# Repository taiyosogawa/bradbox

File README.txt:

==========
= README =
==========
Author: Taiyo Sogawa
Last Revised: 3/17/2013

=======================
= System Requirements =
=======================
Device: Windows XP 32-bit Operating System

1) Install Java SE 7 JRE
	See:	<http://www.oracle.com/technetwork/java/javase/downloads/index.html>

============================
= Application Installation =
============================

1) Double click on Install_Brad_Box.exe
	This should automatically:
		Put the platform-tools directory in the root directory (Do not delete C:\platform-tools after installation!)
		Put rxtxSerial.dll, sqlite3.def, sqlite3.dll, and sqlite3.exe in C:\WINDOWS\System32
		Put an "Brad Box.exe" on the desktop
	If anything fails, make sure these files are located in the appropriate directories. Manually copying the files might be necessary.

========================
= Arduino Installation =
========================
Device: Arduino Micro

1) Install Driver for Arduino Micro 
	Drivers are located in the setup/arduino-drivers directory 
2) Change device port to COM34
	Control Panel > System Properties > Device Manager
	Find Arduino Micro under Ports
	Right Click > Properties > Port Settings > Advanced
	Change port number to COM34

========================
= Android Installation =
========================
Device: Unlocked Samsung Galaxy Pocket S5300

1) Install phone drivers on computer (Directions vary by device.)
	Drivers for Galaxy Pocket are in the setup/android-drivers directory
2) Factory reset the phone if desired (Directions vary by device.)
	On the Galaxy Pocket, Dial *2767*3855#
3) Root the android phone (Directions vary by device.)
4) Enable USB Debug Mode (Directions vary by device.)
	On the Galaxy Pocket, Settings > Applications > Development > USB debugging 
5) Install Android application
	Connect phone to computer by USB
	You can check the connection by opening CMD, navigating to C:\platform-tools and typing command "adb devices"
	Double click install_new_android_application.exe in C:\platform-tools when phone connected
	You will see the Brad Box logo on the phone screen on a successful install

============================
= Additional Documentation =
============================

https://code.google.com/p/aster/source/browse/src/com/android/chimpchat/core/IChimpDevice.java?r=967f7f8cd6249c69e00c6de7ff1b55bd0f51d311

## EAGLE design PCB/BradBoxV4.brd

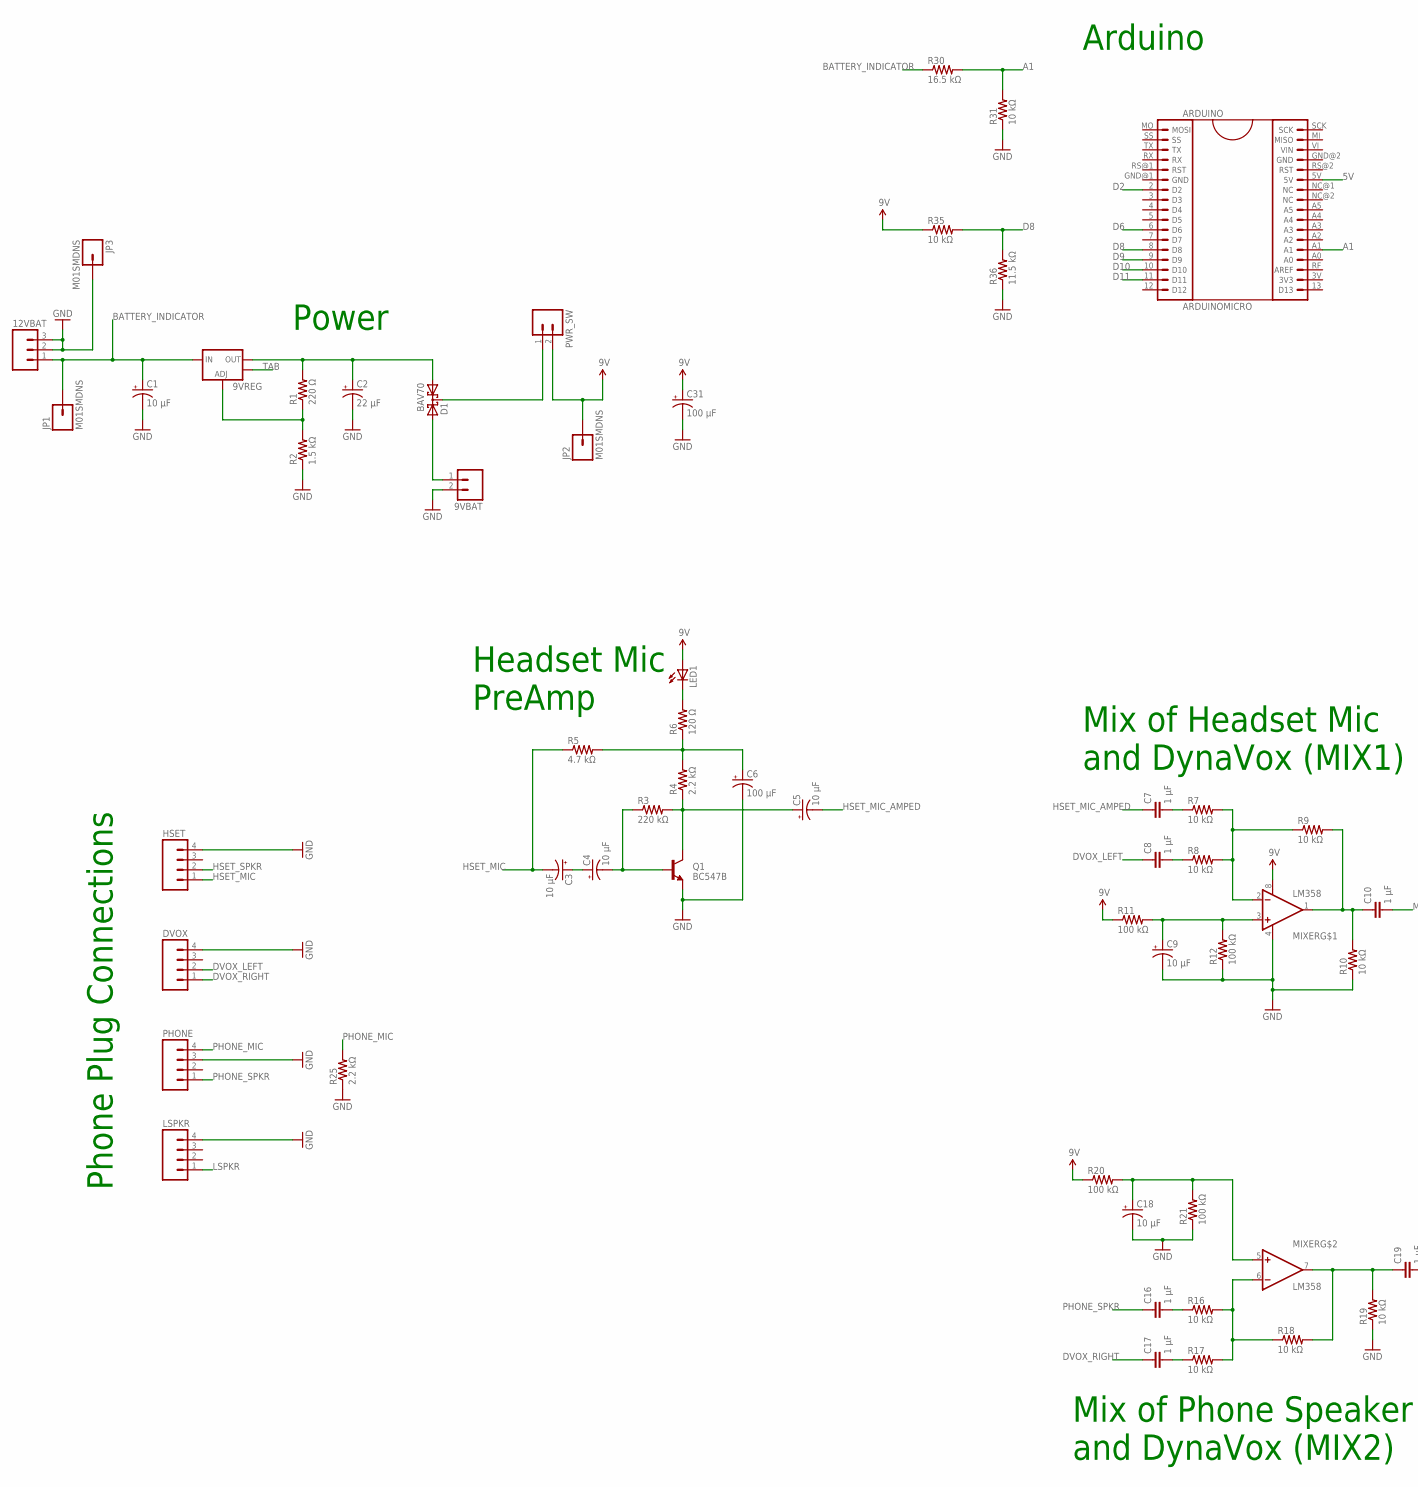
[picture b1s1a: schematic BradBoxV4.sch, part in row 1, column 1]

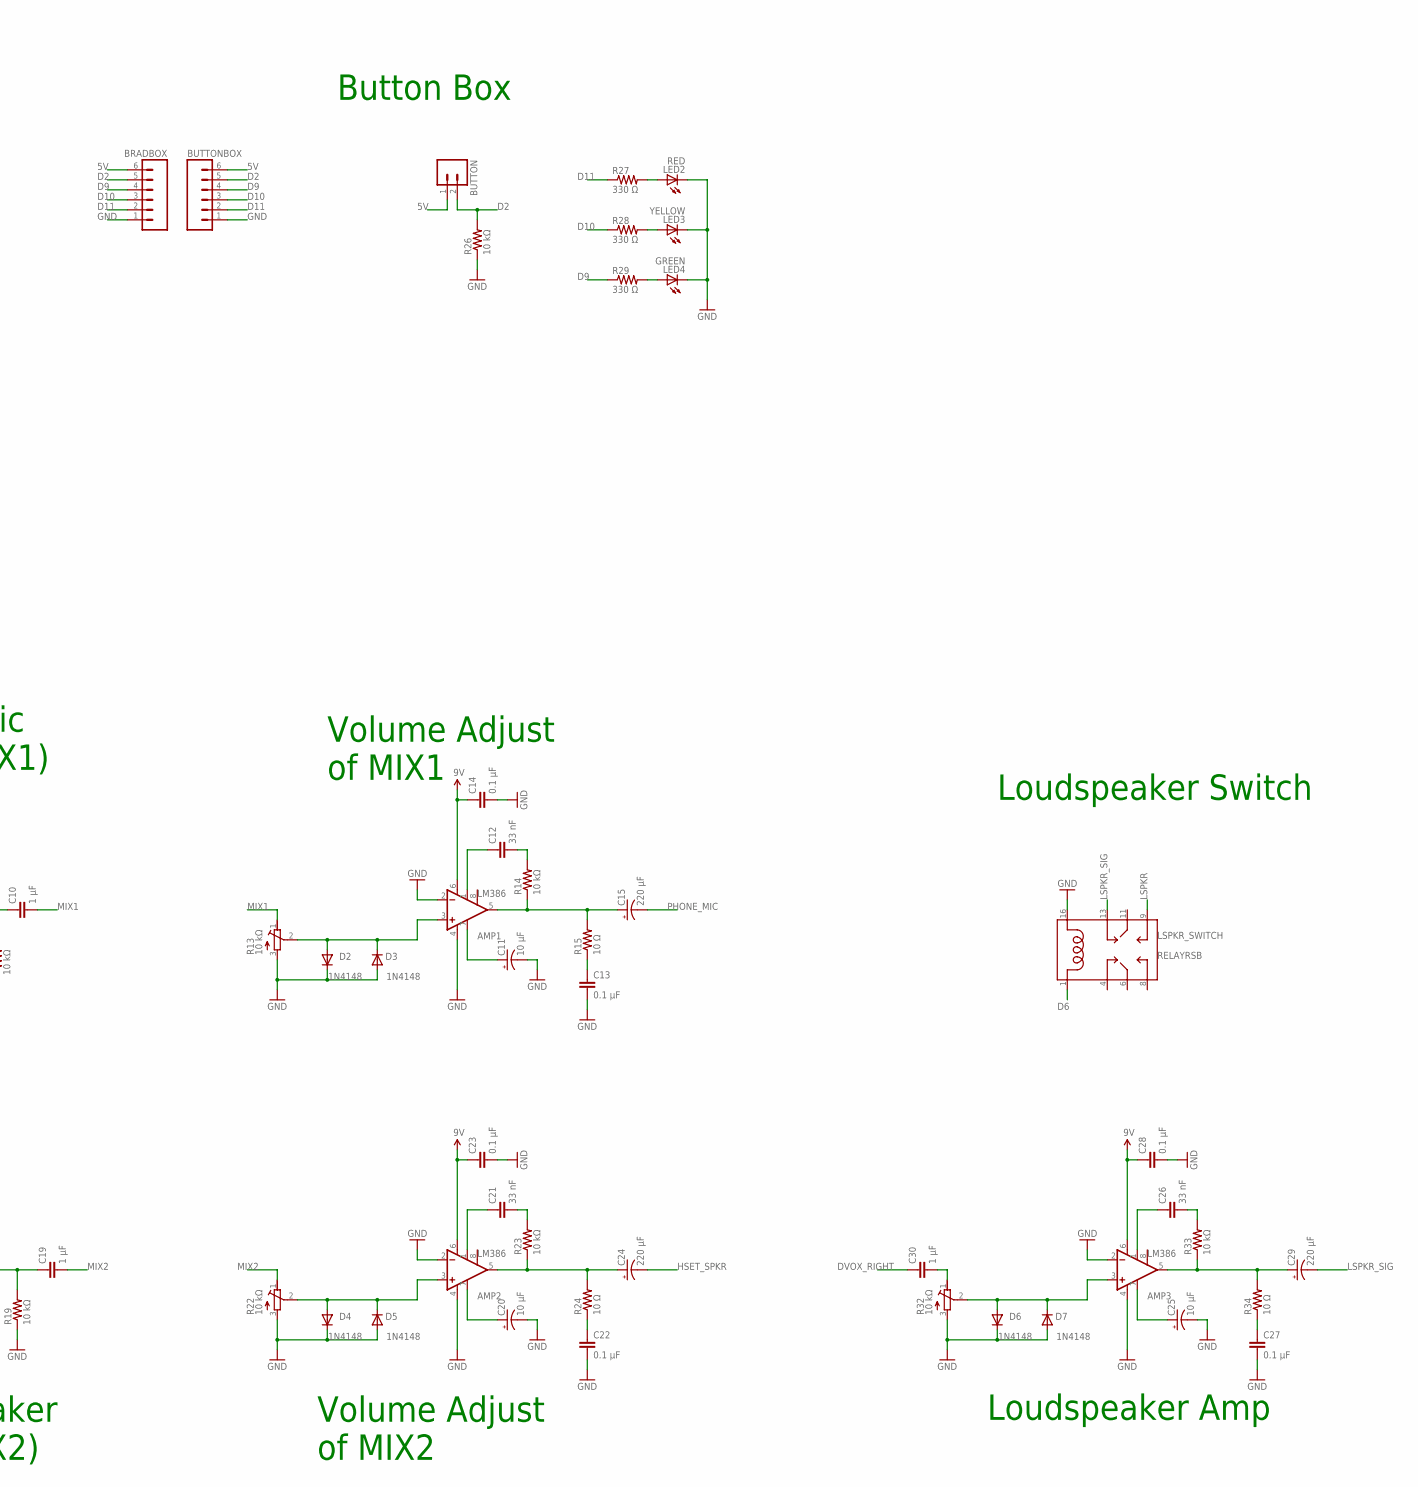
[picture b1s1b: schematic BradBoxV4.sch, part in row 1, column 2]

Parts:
9VBAT: M02POLAR; MOLEX-1X2
9VREG: V_REG_LM1117SOT223; SOT223
12VBAT: M03POLAR; MOLEX-1X3
AMP1, AMP2, AMP3: LM386; DIP08
ARDUINO: ARDUINOMICRO; ARDUINO_MICRO
BRADBOX: M06POLAR; MOLEX-1X6
BUTTON: M02POLAR; MOLEX-1X2
BUTTONBOX: M06POLAR; MOLEX-1X6
C1, C3, C4, C5, C9, C11, C18, C20, C25: 10 µF; 0603-CAP-POL
C2: 22 µF; 0603-CAP-POL
C6, C31: 100 µF; CPOL-RADIAL-100UF-100V
C7, C8, C10, C16, C17, C19, C30: 1 µF; 0603-CAP
C12, C21, C26: 33 nF; 0603-CAP
C13, C14, C22, C23, C27, C28: 0.1 µF; 0603-CAP
C15, C24, C29: 220 µF; CPOL-RADIAL-220UF-100V
D1: BAV70; SOT23
D2, D3, D4, D5, D6, D7: 1N4148; SOD523F
DVOX: M04POLAR; MOLEX-1X4
HSET: M04POLAR; MOLEX-1X4
JP1, JP2, JP3: M01SMDNS; 1X01NS
LED1: LED0603; LED-0603
LED2: RED; LED5MM
LED3: YELLOW; LED5MM
LED4: GREEN; LED5MM
LSPKR: M04POLAR; MOLEX-1X4
LSPKR_SWITCH: RELAYRSB; RELAY-RSB
MIXER: LM358; DIP08
PHONE: M04POLAR; MOLEX-1X4
PWR_SW: M02POLAR; MOLEX-1X2
Q1: BC547B; TO-92-AMMO
R1: 220 Ω; R0603
R2: 1.5 kΩ; R0603
R3: 220 kΩ; R0603
R4, R25: 2.2 kΩ; R0603
R5: 4.7 kΩ; R0603
R6: 120 Ω; R0603
R7, R8, R9, R10, R14, R16, R17, R18, R19, R23, R26, R31, R33, R35: 10 kΩ; R0603
R11, R12, R20, R21: 100 kΩ; R0603
R13, R22, R32: 10 kΩ; RTRIMT93YA
R15, R24, R34: 10 Ω; R0603
R27, R28, R29: 330 Ω; R0603
R30: 16.5 kΩ; R0603
R36: 11.5 kΩ; R0603

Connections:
5V: ARDUINO.5V, BRADBOX.6, BUTTON.1, BUTTONBOX.6
9V: AMP1.6 (V+), AMP2.6 (V+), AMP3.6 (V+), C14.1, C23.1, C28.1, C31.1 (+), JP2.1, LED1.A, MIXER.8 (V+), PWR_SW.2, R11.1, R20.1, R35.1
A1: ARDUINO.A1, R30.2, R31.2
BATTERY_INDICATOR: 9VREG.3 (IN), 12VBAT.1, C1.1 (+), JP1.1, R30.1
D2: ARDUINO.2 (D2), BRADBOX.5, BUTTON.2, BUTTONBOX.5, R26.2
D6: ARDUINO.6 (D6), LSPKR_SWITCH.1
D8: ARDUINO.8 (D8), R35.2, R36.2
D9: ARDUINO.9 (D9), BRADBOX.4, BUTTONBOX.4, R29.1
D10: ARDUINO.10 (D10), BRADBOX.3, BUTTONBOX.3, R28.1
D11: ARDUINO.11 (D11), BRADBOX.2, BUTTONBOX.2, R27.1
DVOX_LEFT: C8.1, DVOX.2
DVOX_RIGHT: C17.1, C30.1, DVOX.1
GND: 9VBAT.2, 12VBAT.2, 12VBAT.3, AMP1.2 (-IN), AMP1.4 (V-), AMP2.2 (-IN), AMP2.4 (V-), AMP3.2 (-IN), AMP3.4 (V-), BRADBOX.1, BUTTONBOX.1, C1.2 (-), C2.2 (-), C6.2 (-), C9.2 (-), C11.2 (-), C13.2, C14.2, C18.2 (-), C20.2 (-), C22.2, C23.2, C25.2 (-), C27.2, C28.2, C31.2 (-), D2.C, D3.A, D4.C, D5.A, D6.C, D7.A, DVOX.4, HSET.4, JP3.1, LED2.K (C), LED3.K (C), LED4.K (C), LSPKR.4, LSPKR_SWITCH.16, MIXER.4 (V-), PHONE.3, Q1.1 (E), R2.1, R10.1, R12.1, R13.3 (E), R19.1, R21.1, R22.3 (E), R25.1, R26.1, R31.1, R32.3 (E), R36.1
HSET_MIC: C3.2 (-), HSET.1, R5.1
HSET_MIC_AMPED: C5.2 (-), C7.1
HSET_SPKR: C24.2 (-), HSET.2
LSPKR: LSPKR.1, LSPKR_SWITCH.9
LSPKR_SIG: C29.2 (-), LSPKR_SWITCH.13
MIX1: C10.2, R13.1 (A)
MIX2: C19.2, R22.1 (A)
unnamed: 9VREG.2 (OUT), C2.1 (+), D1.1 (A1), R1.2
unnamed: 9VREG.1 (ADJ), R1.1, R2.2
unnamed: AMP3.3 (+IN), D6.A, D7.C, R32.2 (S)
unnamed: D1.3 (C), PWR_SW.1
unnamed: 9VBAT.1, D1.2 (A2)
unnamed: C3.1 (+), C4.1 (+)
unnamed: C4.2 (-), Q1.2 (B), R3.1
unnamed: C5.1 (+), Q1.3 (C), R3.2, R4.1
unnamed: LED1.C, R6.2
unnamed: C6.1 (+), R4.2, R5.2, R6.1
unnamed: C8.2, R8.1
unnamed: C7.2, R7.1
unnamed: MIXER.2 (-IN), R7.2, R8.2, R9.1
unnamed: C10.1, MIXER.1 (OUT), R9.2, R10.2
unnamed: C9.1 (+), MIXER.3 (+IN), R11.2, R12.2
unnamed: AMP1.1 (GAIN), C12.1
unnamed: C12.2, R14.2
unnamed: AMP1.3 (+IN), D2.A, D3.C, R13.2 (S)
unnamed: AMP1.5 (OUT), C15.1 (+), R14.1, R15.2
unnamed: AMP1.7 (BP), C11.1 (+)
unnamed: C13.1, R15.1
unnamed: C17.2, R17.1
unnamed: C16.2, R16.1
unnamed: C18.1 (+), MIXER.5 (+IN), R20.2, R21.2
unnamed: MIXER.6 (-IN), R16.2, R17.2, R18.1
unnamed: C19.1, MIXER.7 (OUT), R18.2, R19.2
unnamed: AMP2.3 (+IN), D4.A, D5.C, R22.2 (S)
unnamed: AMP2.7 (BP), C20.1 (+)
unnamed: AMP2.1 (GAIN), C21.1
unnamed: C21.2, R23.2
unnamed: AMP2.5 (OUT), C24.1 (+), R23.1, R24.2
unnamed: C22.1, R24.1
unnamed: LED2.A, R27.2
unnamed: LED3.A, R28.2
unnamed: LED4.A, R29.2
unnamed: AMP3.7 (BP), C25.1 (+)
unnamed: AMP3.1 (GAIN), C26.1
unnamed: C26.2, R33.2
unnamed: AMP3.5 (OUT), C29.1 (+), R33.1, R34.2
unnamed: C27.1, R34.1
unnamed: C30.2, R32.1 (A)
PHONE_MIC: C15.2 (-), PHONE.4, R25.2
PHONE_SPKR: C16.1, PHONE.1
TAB: 9VREG.4 (OUT)

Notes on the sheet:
Phone Plug Connections
Power
Headset Mic PreAmp
Mix of Headset Mic and DynaVox (MIX1)
Volume Adjust of MIX1
Mix of Phone Speaker and DynaVox (MIX2)
Volume Adjust of MIX2
Arduino
Button Box
Loudspeaker Amp
Loudspeaker Switch

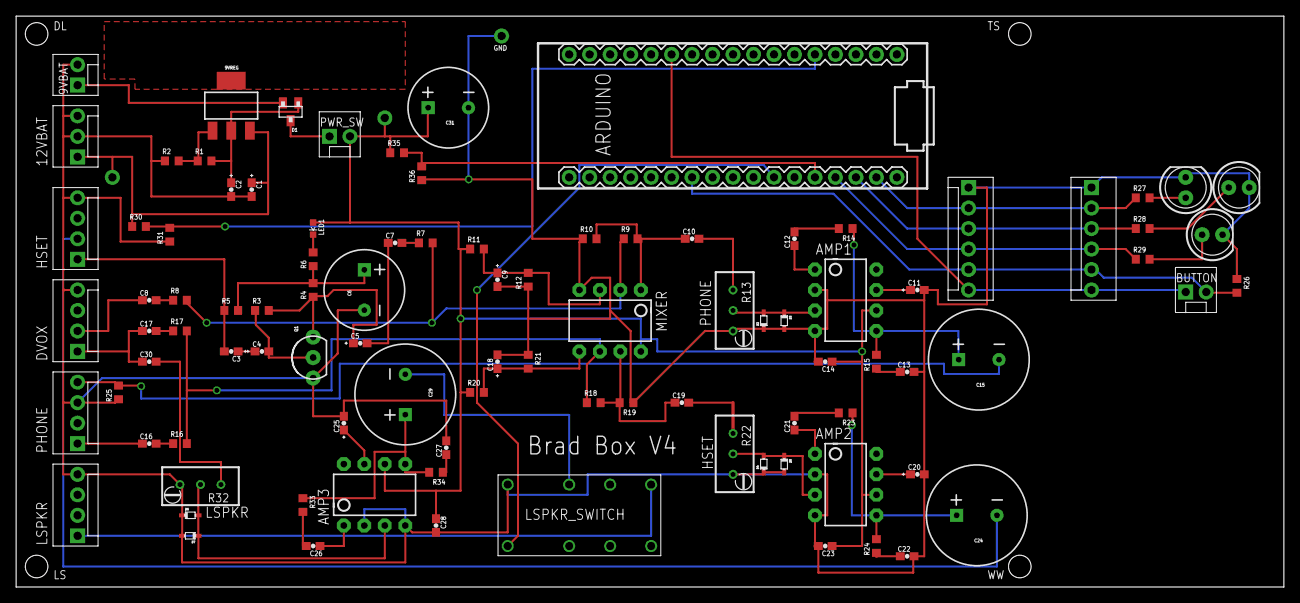
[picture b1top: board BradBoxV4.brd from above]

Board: 2 copper layers, 157.2 x 70.8 mm, 99 parts (0 on the bottom side), 63 nets.

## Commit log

2013-01-28 First commit with Java
2013-01-28 Calls can now be initiated and ended correctly
2013-01-28 Button push from Arduino will push the call button on the phone
2013-01-30 created separate classes for SuperFrame and KeypadPanel
2013-01-30 call, end call are public functions, Interface Constants defined
2013-02-04 Long button presses will restart the phone.
2013-02-04 can send hardcoded sms
2013-02-04 can send dynamic sms to phone numbers
2013-02-04 Changed navigation button icons
2013-02-04 Added all images for navigation buttons
2013-02-06 Grouped JToggleButtons
2013-02-06 Changed Look and Feel
2013-02-06 Added texting button
2013-02-06 added texting images
2013-02-18 removed platform-tools from project
2013-02-18 texting panel.
2013-02-21 Changed Keypad Button Sizes
2013-02-23 keypad shows up on phone when switching to keypad panel
2013-02-23 added images
2013-02-24 Device restarts with long button press
2013-02-24 contacts database automatically copies when a contact is added
2013-02-25 can search for contacts when pushing search button
2013-02-25 Added readme
2013-03-03 Loudspeaker controlled from options menu (pin 3 high = loudspeaker on)
2013-03-03 keys perform search query by name or number
2013-03-04 favorites or top 3 search results displayed on keypadPanel
2013-03-04 call button on ContactModule will dial and call correct number
2013-03-04 will delete up to 10 extra digits on phone before dialing
2013-03-04 Contacts can be deleted through editContactPanel
2013-03-04 Contacts edited by deleting old contact then creating new contact with new information.
2013-03-10 interface layout updated
2013-03-11 phone wakes up and unlocks when dialing.
2013-03-11 contacts can be saved as favorites
2013-03-11 Favorites added, edited, and deleted properly.
2013-03-15 Panels use consistent navigation
2013-03-15 fixed adding new contact as favorite
2013-03-15 Volume Panel works
2013-03-16 numbers prettified
2013-03-16 Checkbox is bigger size
2013-03-17 Serialio listens on COM34
2013-03-17 license updated
2013-03-17 updated for 800x600 resolution
2013-03-18 PCB schematics included.
2013-03-18 keypad is shown upon deleting a contact
2013-03-18 added files for brad box and push button box
2013-04-24 updated Arduino code with debounce and no restart option
2013-05-31 Updated arduino code to send 'short' and 'long' messages
2013-05-31 long button push will start and restart BradTrack
